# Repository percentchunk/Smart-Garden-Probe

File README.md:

# Smart Garden Probe

The Smart Garden Probe is a small plant-monitoring device built around the Seeed Studio XIAO RP2040. It uses a soil sensor and OLED display to show soil moisture, temperature, and whether the plant is in a good range.

## Overview

This project started as a three-key Hackpad, but I wanted it to do something more useful than keyboard shortcuts, and complex enough that it stands on its own.

The device has three buttons, an OLED display, and an I2C soil sensor. The sensor reads soil moisture and temperature, and the screen shows the readings along with a simple status such as Too Dry, Good, or Too Wet.

The firmware also uses plant profiles. Each profile stores the moisture and temperature ranges for a specific plant, you can edit this with the database in the github.

## Features

* Seeed Studio XIAO RP2040
* Three MX-style switches
* SSD1306 I2C OLED
* I2C capacitive soil sensor
* Custom two-layer PCB
* Custom 3D-printed enclosure
* USB-C power
* Plant profile system
* Moisture and temperature shown together
* Gerber, drill, and STEP files included

## Project Views

| Top View                                                                                                                 | Front View                                                                                                                 | PCB View                                                                                                                 |
| ------------------------------------------------------------------------------------------------------------------------ | -------------------------------------------------------------------------------------------------------------------------- | ------------------------------------------------------------------------------------------------------------------------ |
|  |  |  |

## How It Works

The soil sensor sends moisture and temperature readings to the XIAO RP2040 over I2C.

The firmware compares the readings with the selected plant profile. The OLED then shows the plant name, moisture, temperature, and status.

The three buttons are used to refresh the readings, change the plant profile, and control the display.

## Button Functions

| Button | Function                    |
| ------ | --------------------------- |
| SW1    | Refresh the sensor readings |
| SW2    | Change the plant profile    |
| SW3    | Turn the display on or off  |

## Hardware

| Part            | Details                                  |
| --------------- | ---------------------------------------- |
| Microcontroller | Seeed Studio XIAO RP2040                 |
| Display         | 128×64 SSD1306 I2C OLED                  |
| Sensor          | I2C soil moisture and temperature sensor |
| Inputs          | Three MX-style switches                  |
| Power           | USB-C                                    |
| PCB             | Custom two-layer KiCad PCB               |
| Enclosure       | 3D-printed top and bottom case           |

## PCB

The PCB was designed in KiCad and is about 62.5 mm by 62.5 mm.

It includes:

* The XIAO RP2040
* Three switch footprints
* OLED header
* Soil sensor header
* Four 2.5 mm mounting holes

## Cad

The pad was designed in Onshape.

I added the PCB model to the CAD assembly so I could check the mounting holes, headers, USB-C port, switches, OLED, and cable opening.

The mounting holes and clearances were corrected after checking the PCB inside the case.

## Firmware

The firmware is designed to:

* Read the soil sensor
* Show moisture and temperature
* Compare readings with plant profiles
* Show simple status messages
* Change profiles with SW2
* Refresh readings with SW1
* Control the display with SW3

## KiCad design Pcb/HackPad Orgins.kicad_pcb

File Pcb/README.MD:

PCB Files
This folder contains the KiCad PCB design files and manufacturing outputs for the Smart Garden Probe Hackpad.

The PCB is a custom 2-layer board built around the Seeed XIAO RP2040. It includes three MX-style switch inputs, an OLED I2C header, and an I2C soil sensor header.

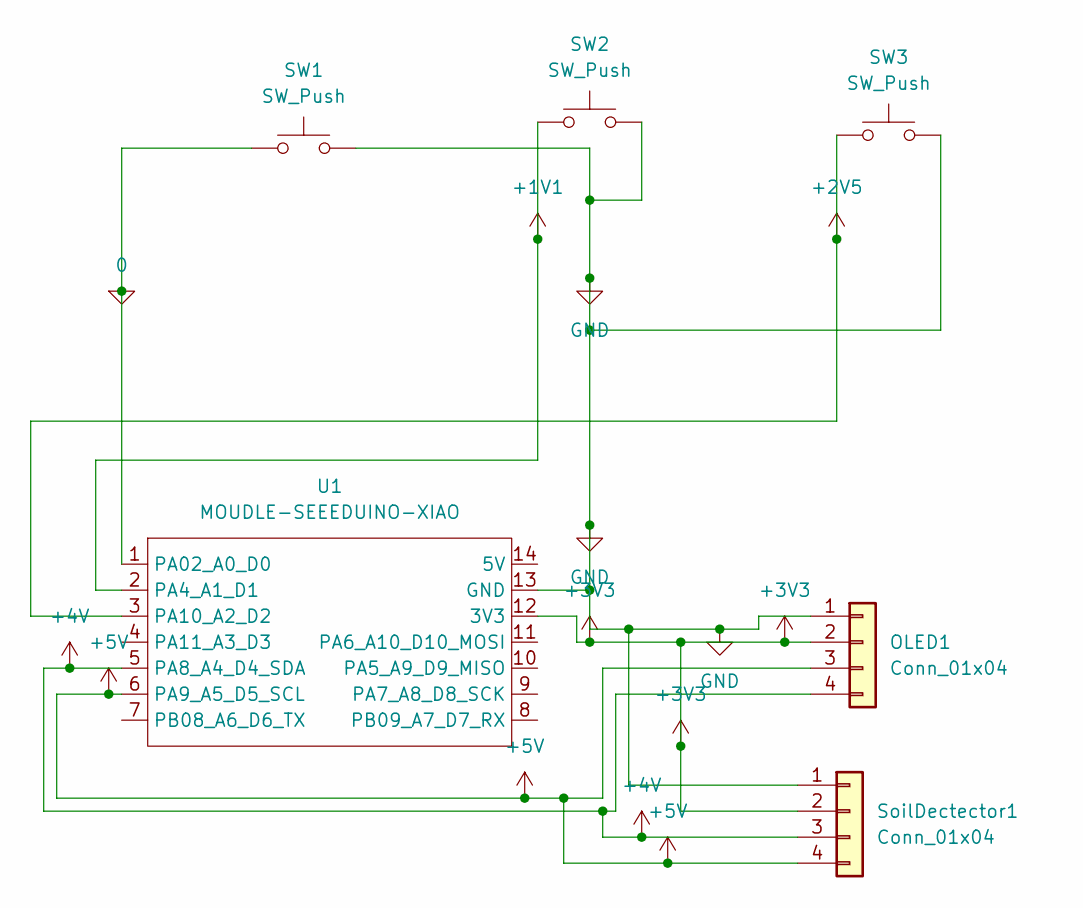
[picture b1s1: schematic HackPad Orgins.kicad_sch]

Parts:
OLED1: Conn_01x04; FanPinHeader_1x04_P2.54mm_Vertical
SW1, SW2, SW3: SW_Push; SW_Cherry_MX_1.00u_PCB
SoilDectector1: Conn_01x04; FanPinHeader_1x04_P2.54mm_Vertical
U1: MOUDLE-SEEEDUINO-XIAO; XIAO-Generic-Hybrid-14P-2.54-21X17.8MM

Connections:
0: SW1.1, U1.1 (PA02_A0_D0)
+1V1: SW2.1, U1.2 (PA4_A1_D1)
+2V5: SW3.1, U1.3 (PA10_A2_D2)
+3V3: OLED1.2, SoilDectector1.2, U1.12 (3V3)
+4V: OLED1.4, SoilDectector1.3, U1.5 (PA8_A4_D4_SDA)
+5V: OLED1.3, SoilDectector1.4, U1.6 (PA9_A5_D5_SCL)
GND: OLED1.1, SW1.2, SW2.2, SW3.2, SoilDectector1.1, U1.13 (GND)

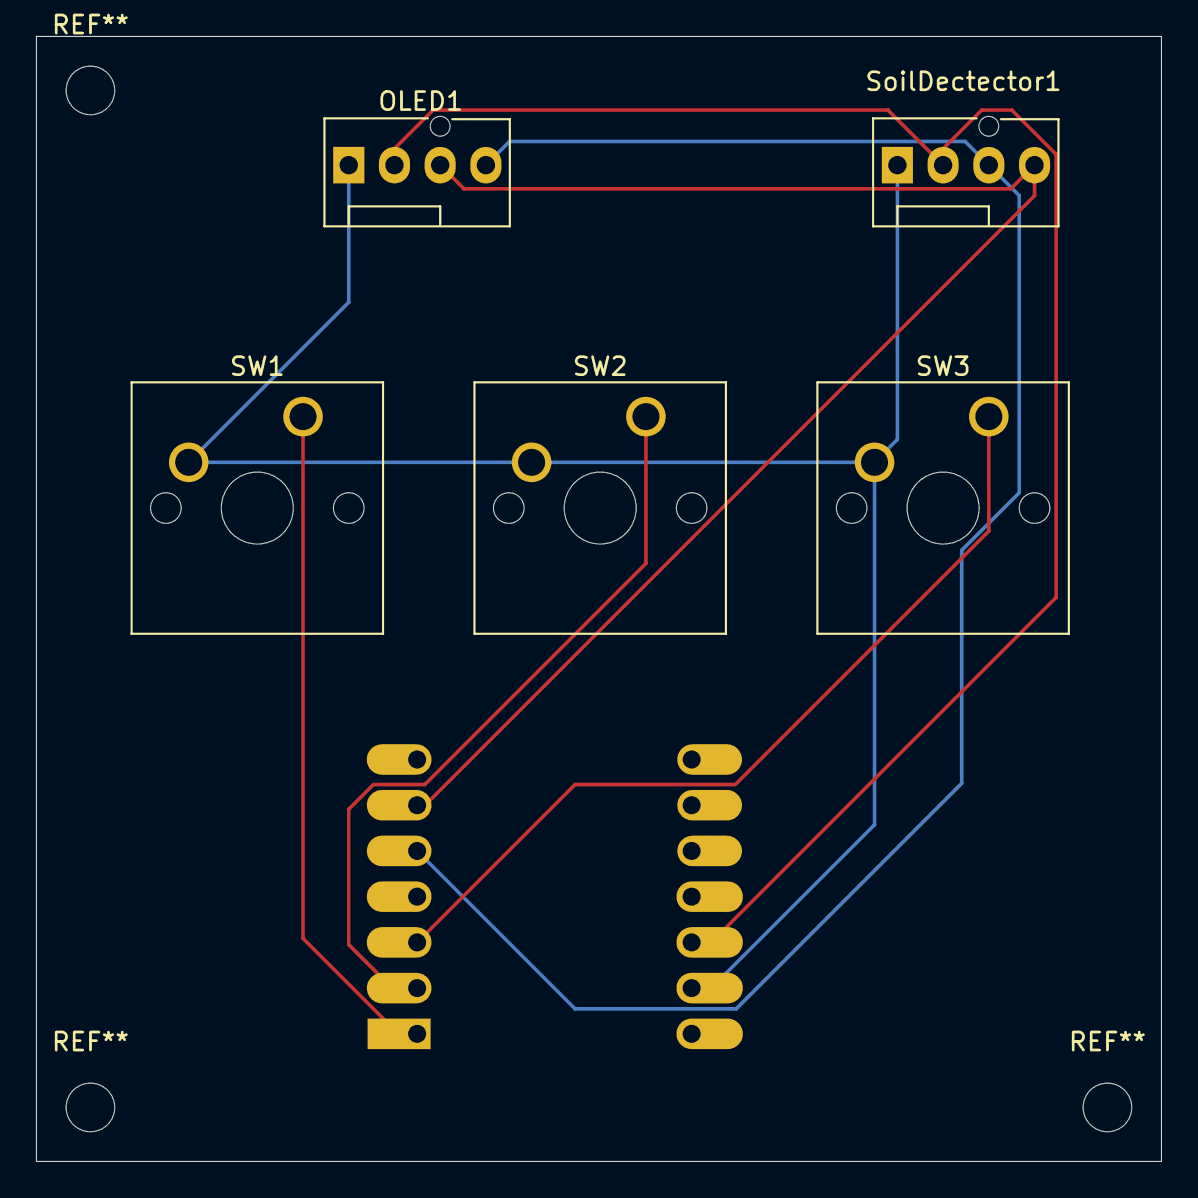
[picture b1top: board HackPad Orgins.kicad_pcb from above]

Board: 2 copper layers, 62.5 x 62.5 mm, 6 parts (1 on the bottom side), 7 nets.

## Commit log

2026-06-18 Add files via upload
    Add firmware starter and profile test
2026-06-18 Update README.md
    I think im done lowkey
2026-06-24 Journal.md
2026-06-26 Rename BOM.md to BOM.csv
